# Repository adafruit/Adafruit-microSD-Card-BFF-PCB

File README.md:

## Adafruit microSD Card BFF Add-On for QT Py and Xiao PCB

<a href="http://www.adafruit.com/products/5683"><br/>
Click here to purchase one from the Adafruit shop</a>

PCB files for the Adafruit microSD Card BFF Add-On for QT Py and Xiao. 

Format is EagleCAD schematic and board layout
* https://www.adafruit.com/product/5683

### Description

Our QT Py boards are a great way to make very small microcontroller projects that pack a ton of power - and now we have a way for you to add a ton of storage, for reading and writing, with a micro SD card slot that can fit on the back of your miniature dev board. It uses the three SPI pins plus one chip select pin to access megs or gigs of data.

We call this the Adafruit microSD BFF - a "Best Friend Forever". When you were a kid you may have learned about the "buddy" system, well this product is kinda like that! A board that will watch your QT Py's back and give it more capabilities.

This PCB is designed to fit onto the back of any QT Py or Xiao board, it can be soldered into place or use pin and socket headers to make it removable. Onboard is a slim, high quality Molex push-pull micro SD card socket. Since the QT Py is already 3V, no level shifter or regulator is required. We're using SPI mode to interface, use the MOSI/MISO/SCK pins plus one other chip select pin. The default is TX but there are some solder jumpers you can use to select RX, A0 or A1.

We include some header that you can solder to your QT Py. You can also pick up an Itsy Bitsy short female header kit to make it removable but compact, you'll just need to trim down the headers to 7 pins long.

* Comes as an assembled and tested PCB
* For any QT Py or Xiao boards
* Use any micro SD card that supports SPI mode with one CS pin.
* Any Arduino / CircuitPython / MicroPython library can be used to talk to the card just like a normal SD card breakout!

microSD card and QT Py are not included.

### License

Adafruit invests time and resources providing this open source design, please support Adafruit and open-source hardware by purchasing products from [Adafruit](https://www.adafruit.com)!

Designed by Limor Fried/Ladyada for Adafruit Industries.

Creative Commons Attribution/Share-Alike, all text above must be included in any redistribution. 
See license.txt for additional details.

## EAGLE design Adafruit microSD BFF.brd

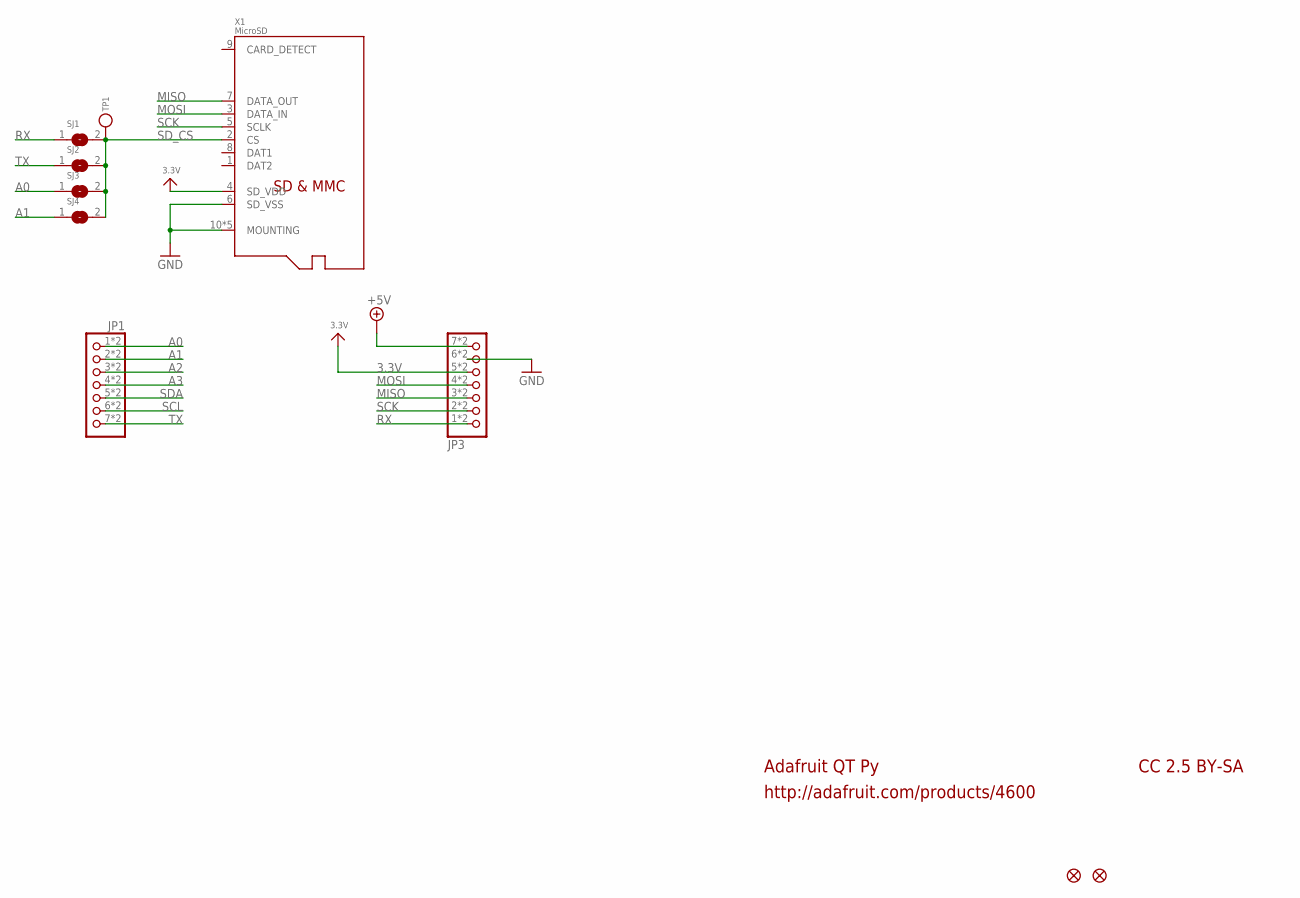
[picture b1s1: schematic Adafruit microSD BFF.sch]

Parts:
JP1, JP3: HEADER-1X7_CASTEL; 1X07_CASTEL
SJ1, SJ3, SJ4: SOLDERJUMPER; SOLDERJUMPER_ARROW_NOPASTE
SJ2: SOLDERJUMPERCLOSED; SOLDERJUMPER_CLOSEDWIRE
TP1: TESTPOINTPAD1MM; TESTPOINT_PAD_1MM
U$6, U$8: FIDUCIAL_1MM
X1: MicroSD; MOLEX_104031-0811

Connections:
3.3V: JP3.5, JP3.5C (5), X1.4 (SD_VDD)
+5V: JP3.7, JP3.7C (7)
A0: JP1.1, JP1.1C (1), SJ3.1
A1: JP1.2, JP1.2C (2), SJ4.1
A2: JP1.3, JP1.3C (3)
A3: JP1.4, JP1.4C (4)
GND: JP3.6, JP3.6C (6), X1.6 (SD_VSS), X1.10 (MOUNTING), X1.G1 (MOUNTING), X1.G2 (MOUNTING), X1.G3 (MOUNTING), X1.G4 (MOUNTING)
MISO: JP3.3, JP3.3C (3), X1.7 (DATA_OUT)
MOSI: JP3.4, JP3.4C (4), X1.3 (DATA_IN)
RX: JP3.1, JP3.1C (1), SJ1.1
SCK: JP3.2, JP3.2C (2), X1.5 (SCLK)
SCL: JP1.6, JP1.6C (6)
SDA: JP1.5, JP1.5C (5)
SD_CS: SJ1.2, SJ2.2, SJ3.2, SJ4.2, TP1.P$1, X1.2 (CS)
TX: JP1.7, JP1.7C (7), SJ2.1

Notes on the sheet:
Adafruit QT Py
http://adafruit.com/products/4600
CC 2.5 BY-SA

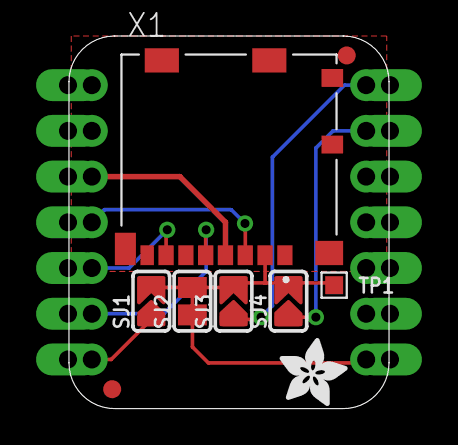
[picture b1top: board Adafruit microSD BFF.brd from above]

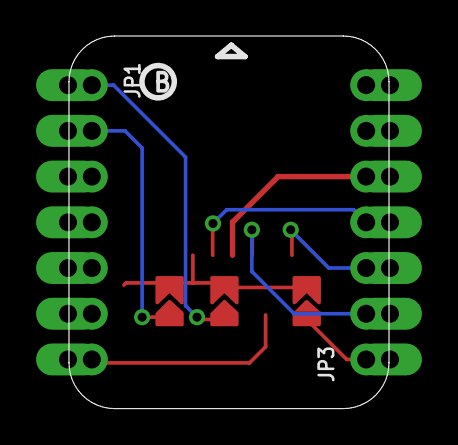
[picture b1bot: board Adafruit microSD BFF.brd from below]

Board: 2 copper layers, 17.8 x 20.7 mm, 20 parts (5 on the bottom side), 15 nets.

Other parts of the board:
PLABEL0: PLABEL0
PLABEL1: PLABEL1
PLABEL2: PLABEL2
PLABEL3: PLABEL3
PLABEL4: PLABEL4
PLABEL5: PLABEL5
PLABEL6: PLABEL6
PLABEL7: PLABEL7
U$2: ADAFRUIT_3.5MM
U$3: PCBFEAT-REV-040

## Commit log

2023-02-13 adding cookiecutter output
2023-02-13 updating readme

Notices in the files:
parts and their libraries:
microbuilder: This work is placed in the public domain, and may be freely used for commercial and non-commercial work with the following conditions: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
